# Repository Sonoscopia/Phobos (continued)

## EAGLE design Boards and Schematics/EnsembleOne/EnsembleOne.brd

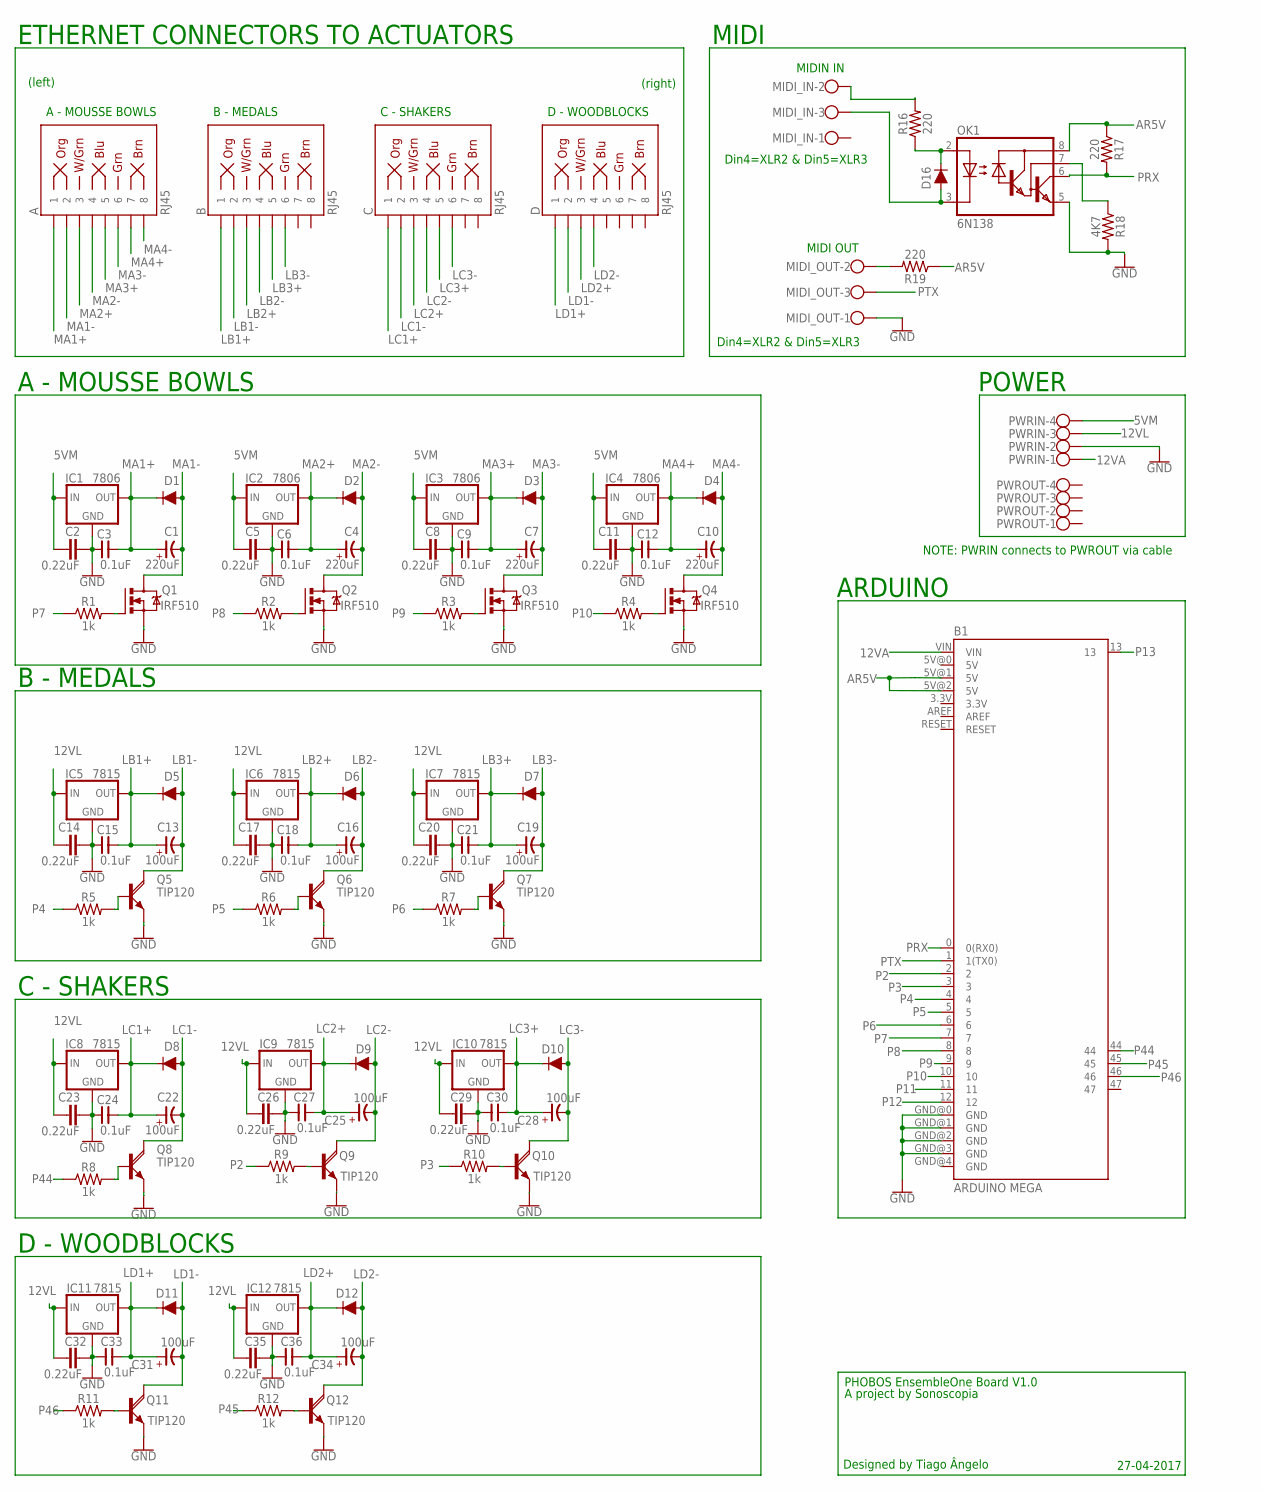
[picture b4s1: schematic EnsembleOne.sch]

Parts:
A: RJ45; RJ45-8
B: RJ45; RJ45-8
B1: ARDUINO MEGA; ENSEMBLE_ONE_ARDUINO_MEGA
C: RJ45; RJ45-8
C1, C4, C7, C10: 220uF; E-035X080
C2, C5, C8, C11, C14, C17, C20, C23, C26, C29, C32, C35: 0.22uF; C5B3
C3, C6, C9, C12, C15, C18, C21, C24, C27, C30, C33, C36: 0.1uF; C025-050X025
C13, C16, C19, C22: 100uF; CAP-MASTER_E-020X050
C25, C28, C31, C34: 100uF; E-020X050
D: RJ45; RJ45-8
D1, D2, D3, D4, D5, D6, D7, D8, D9, D10, D11, D12: 1A/50V/1.1V; DIODE-1N4001-KIT
D16: 200mA/100V/1V; DIODE-1N4148
IC1, IC2, IC3, IC4: 7806; 78XXS
IC5, IC6, IC7, IC8, IC9, IC10, IC11, IC12: 7815; 78XXS
MIDI_IN: W237-103
MIDI_OUT: W237-103
OK1: 6N138; DIL08
PWRIN: W237-4
PWROUT: W237-4
Q1, Q2, Q3, Q4: IRF510; TO220BV
Q5, Q6, Q7, Q8: TIP120; ROCKETFARM_TO220AV
Q9, Q10, Q11, Q12: TIP120; TO220AV
R1, R2, R3, R4, R5, R6, R7, R8, R9, R10, R11, R12: 1k; AXIAL-0.1
R16, R17, R19: 220; AXIAL-0.3
R18: 4K7; AXIAL-0.3

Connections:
5VM: C2.1, C5.1, C8.1, C11.1, IC1.IN, IC2.IN, IC3.IN, IC4.IN, PWRIN.4
12VA: B1.VIN, PWRIN.1
12VL: C14.1, C17.1, C20.1, C23.1, C26.1, C29.1, C32.1, C35.1, IC5.IN, IC6.IN, IC7.IN, IC8.IN, IC9.IN, IC10.IN, IC11.IN, IC12.IN, PWRIN.3
AR5V: B1.5V@1 (5V), B1.5V@2 (5V), OK1.8 (VCC), R17.P$1 (1), R19.P$1 (1)
GND: B1.GND@0 (GND), B1.GND@1 (GND), B1.GND@2 (GND), B1.GND@3 (GND), C2.2, C3.1, C5.2, C6.1, C8.2, C9.1, C11.2, C12.1, C14.2, C15.1, C17.2, C18.1, C20.2, C21.1, C23.2, C24.1, C26.2, C27.1, C29.2, C30.1, C32.2, C33.1, C35.2, C36.1, IC1.GND, IC2.GND, IC3.GND, IC4.GND, IC5.GND, IC6.GND, IC7.GND, IC8.GND, IC9.GND, IC10.GND, IC11.GND, IC12.GND, MIDI_OUT.1, OK1.5 (GND), PWRIN.2, Q1.S, Q2.S, Q3.S, Q4.S, Q5.E, Q6.E, Q7.E, Q8.E, Q9.E, Q10.E, Q11.E, Q12.E, R18.P$2 (2)
LB1+: B.1, C13.+, C15.2, D5.C, IC5.OUT
LB1-: B.2, C13.-, D5.A, Q5.C
LB2+: B.3, C16.+, C18.2, D6.C, IC6.OUT
LB2-: B.4, C16.-, D6.A, Q6.C
LB3+: B.5, C19.+, C21.2, D7.C, IC7.OUT
LB3-: B.6, C19.-, D7.A, Q7.C
LC1+: C.1, C22.+, C24.2, D8.C, IC8.OUT
LC1-: C.2, C22.-, D8.A, Q8.C
LC2+: C.3, C25.+, C27.2, D9.C, IC9.OUT
LC2-: C.4, C25.-, D9.A, Q9.C
LC3+: C.5, C28.+, C30.2, D10.C, IC10.OUT
LC3-: C.6, C28.-, D10.A, Q10.C
LD1+: C31.+, C33.2, D.1, D11.C, IC11.OUT
LD1-: C31.-, D.2, D11.A, Q11.C
LD2+: C34.+, C36.2, D.3, D12.C, IC12.OUT
LD2-: C34.-, D.4, D12.A, Q12.C
MA1+: A.1, C1.+, C3.2, D1.C, IC1.OUT
MA1-: A.2, C1.-, D1.A, Q1.D
MA2+: A.3, C4.+, C6.2, D2.C, IC2.OUT
MA2-: A.4, C4.-, D2.A, Q2.D
MA3+: A.5, C7.+, C9.2, D3.C, IC3.OUT
MA3-: A.6, C7.-, D3.A, Q3.D
MA4+: A.7, C10.+, C12.2, D4.C, IC4.OUT
MA4-: A.8, C10.-, D4.A, Q4.D
unnamed: Q1.G, R1.P$2 (2)
unnamed: MIDI_OUT.2, R19.P$2 (2)
unnamed: Q2.G, R2.P$2 (2)
unnamed: Q10.B, R10.P$2 (2)
unnamed: Q11.B, R11.P$2 (2)
unnamed: Q9.B, R9.P$2 (2)
unnamed: Q3.G, R3.P$2 (2)
unnamed: Q4.G, R4.P$2 (2)
unnamed: Q5.B, R5.P$2 (2)
unnamed: Q6.B, R6.P$2 (2)
unnamed: Q7.B, R7.P$2 (2)
unnamed: Q8.B, R8.P$2 (2)
unnamed: Q12.B, R12.P$2 (2)
unnamed: D16.A, MIDI_IN.3, OK1.3 (C)
unnamed: D16.C, OK1.2 (A), R16.P$1 (1)
unnamed: MIDI_IN.2, R16.P$2 (2)
unnamed: OK1.7 (VB), R18.P$1 (1)
P2: B1.2, R9.P$1 (1)
P3: B1.3, R10.P$1 (1)
P4: B1.4, R5.P$1 (1)
P5: B1.5, R6.P$1 (1)
P6: B1.6, R7.P$1 (1)
P7: B1.7, R1.P$1 (1)
P8: B1.8, R2.P$1 (1)
P9: B1.9, R3.P$1 (1)
P10: B1.10, R4.P$1 (1)
P11: B1.11
P12: B1.12
P13: B1.13
P44: B1.44, R8.P$1 (1)
P45: B1.45, R12.P$1 (1)
P46: B1.46, R11.P$1 (1)
PRX: B1.0 (0(RX0)), OK1.6 (VO), R17.P$2 (2)
PTX: B1.1 (1(TX0)), MIDI_OUT.3

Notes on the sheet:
Din4=XLR2 & Din5=XLR3
MIDI OUT
MIDIN IN
POWER
MIDI
ARDUINO
(right)
(left)
ETHERNET CONNECTORS TO ACTUATORS
D - WOODBLOCKS
C - SHAKERS
B - MEDALS
A - MOUSSE BOWLS
PHOBOS EnsembleOne Board V1.0
Designed by Tiago Ângelo
A project by Sonoscopia
27-04-2017
NOTE: PWRIN connects to PWROUT via cable

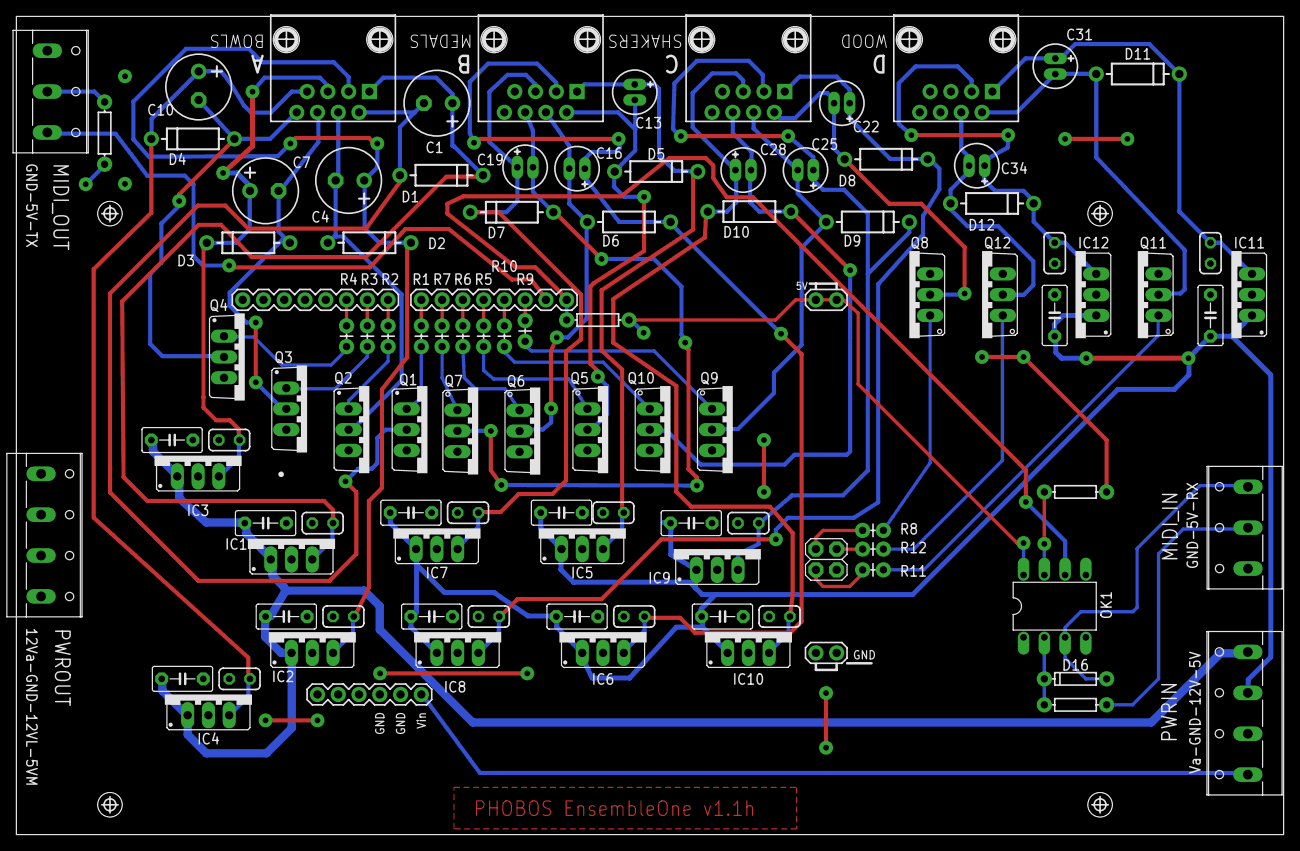
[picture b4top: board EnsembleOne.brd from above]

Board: 2 copper layers, 155.0 x 100.1 mm, 99 parts (0 on the bottom side), 60 nets.

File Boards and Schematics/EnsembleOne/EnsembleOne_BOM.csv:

Partlist exported from C:/Users/tiago/Documents/eagle/PHOBOS/EnsembleOne/EnsembleOne.sch at 05-05-2017 15:47

Qty Value         Device                  Package              Parts                                                   Description               MF                MPN     OC_FARNELL OC_NEWARK PROD_ID    SF_ID     VALUE        
2                 W237-103                W237-103             XIN, XOUT                                               WAGO SCREW CLAMP                            237-103 unknown    18M7116                                     
2                 W237-4                  W237-4               PWRIN, PWROUT                                           WAGO SCREW CLAMP                                    unknown    unknown                                     
12  0.1uF         CNP-C025-050X025        C025-050X025         C3, C6, C9, C12, C15, C18, C21, C24, C27, C30, C33, C36 NON-POLARIZED CAP                                                                                          
12  0.22uF        C5/3                    C5B3                 C2, C5, C8, C11, C14, C17, C20, C23, C26, C29, C32, C35 CAPACITOR                                                                                                  
4   100uF         CAP-MASTER_CP-E-020X050 CAP-MASTER_E-020X050 C13, C16, C19, C22                                      POLARIZED CAP                                                                                              
4   100uF         CP-E-020X050            E-020X050            C25, C28, C31, C34                                      POLARIZED CAP                                                                                              
12  1A/50V/1.1V   DIODE-KIT2              DIODE-1N4001-KIT     D1, D2, D3, D4, D5, D6, D7, D8, D9, D10, D11, D12       Diode                                                                    DIO-09176            1A/50V/1.1V  
12  1k            1KOHM-VERT-1/4W-1%      AXIAL-0.1            R1, R2, R3, R4, R5, R6, R7, R8, R9, R10, R11, R12       1kO resistor                                                             RES-12182            1k           
1   200mA/100V/1V DIODE-1N4148            DIODE-1N4148         D16                                                     Diode                                                                    DIO-08378            200mA/100V/1V
3   220           1KOHM-HORIZ-1/4W-5%     AXIAL-0.3            R16, R17, R19                                           1kO resistor                                                             RES-08380            1k           
4   220uF         CP-E-035X080            E-035X080            C1, C4, C7, C10                                         POLARIZED CAP                                                                                              
1   4K7           1KOHM-HORIZ-1/4W-5%     AXIAL-0.3            R18                                                     1kO resistor                                                             RES-08380            1k           
1   6N138         6N138                   DIL08                OK1                                                     MOTOROLA OPTO COUPLER     VISHAY/TELEFUNKEN 6N138   9860150    35K5294                                     
4   7806          78XXS                   78XXS                IC1, IC2, IC3, IC4                                      VOLTAGE REGULATOR                                                                                          
8   7815          78XXS                   78XXS                IC5, IC6, IC7, IC8, IC9, IC10, IC11, IC12               VOLTAGE REGULATOR                                                                                          
1   ARDUINO MEGA  ARDUINO_MEGA_R3FULL     ARDUINO_MEGA         B1                                                      Arduino Mega R3                                                                                            
4   IRF510        IRF520                  TO220BV              Q1, Q2, Q3, Q4                                          HEXFET Power MOSFET                                                                                        
4   RJ45          RJ45-8                  RJ45-8               A, B, C, D                                              RJ45 Jack - 8 pin                                                        CONN-08506 PRT-00643 RJ45         
4   TIP120        ROCKETFARM_TIP120V      ROCKETFARM_TO220AV   Q5, Q6, Q7, Q8                                          NPN DARLINGTON TRANSISTOR                                                                                  
4   TIP120        TIP120V                 TO220AV              Q9, Q10, Q11, Q12                                       NPN DARLINGTON TRANSISTOR

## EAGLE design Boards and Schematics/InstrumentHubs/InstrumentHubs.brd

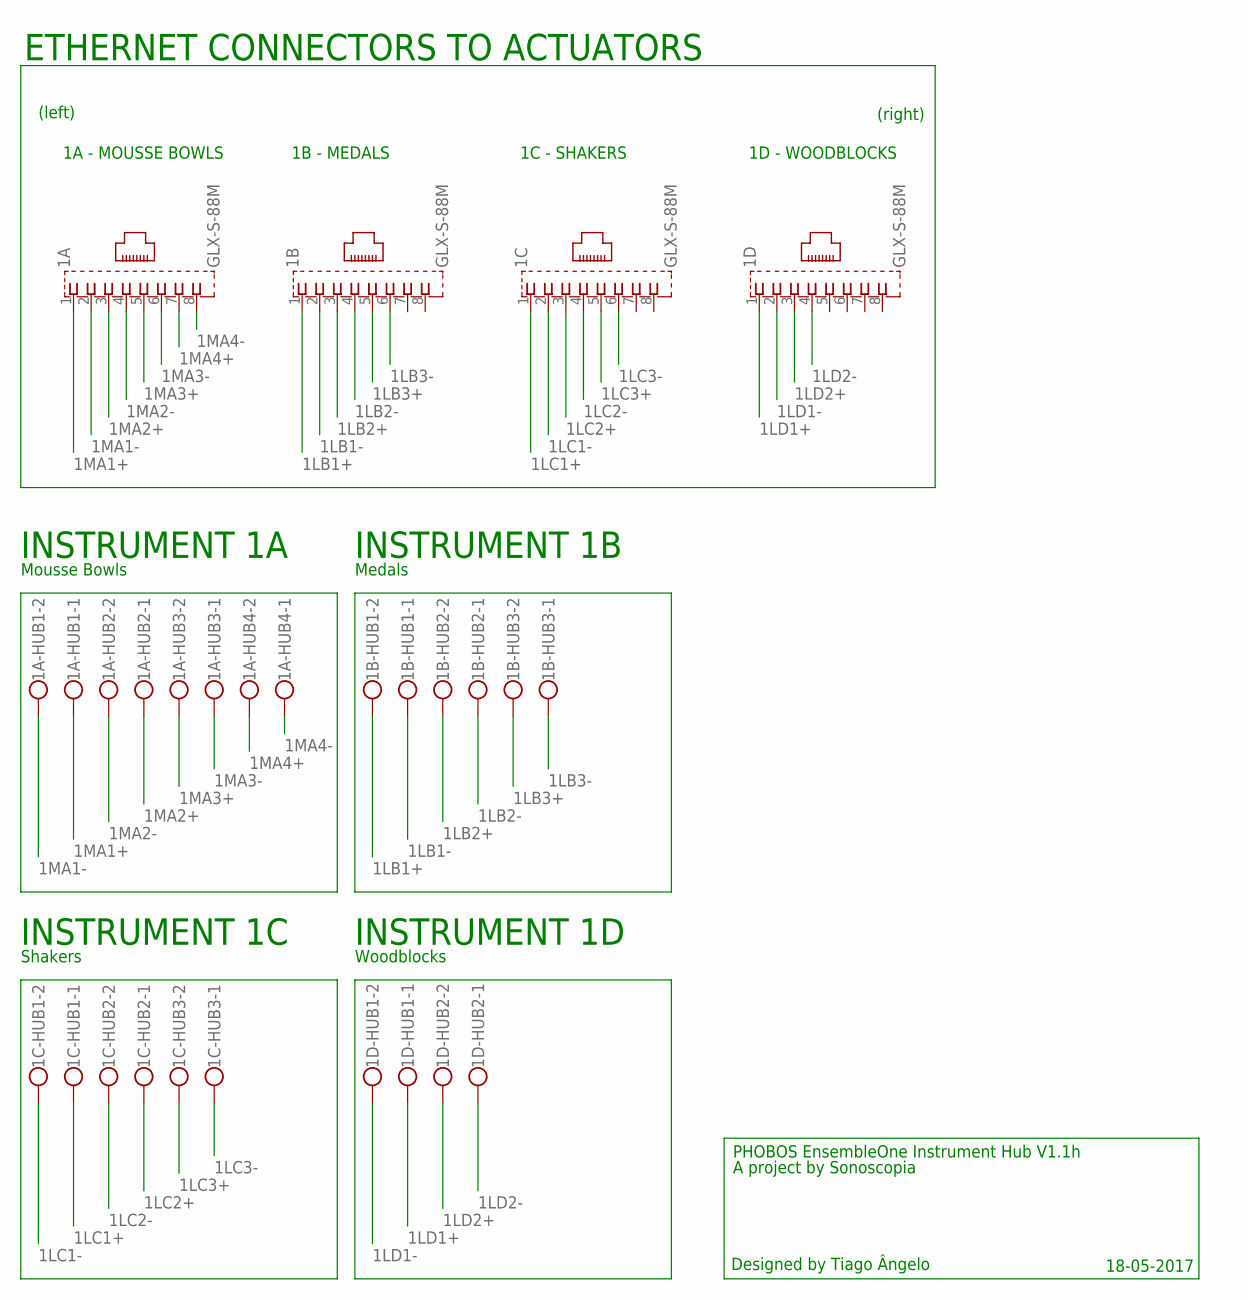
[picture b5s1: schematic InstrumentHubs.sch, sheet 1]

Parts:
1A, 1B, 1C, 1D: GLX-S-88M
1A-HUB1, 1A-HUB2, 1A-HUB3, 1A-HUB4, 1B-HUB1, 1B-HUB2, 1B-HUB3, 1C-HUB1, 1C-HUB2, 1C-HUB3, 1D-HUB1, 1D-HUB2: W237-102

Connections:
1LB1+: 1B.1, 1B-HUB1.2
1LB1-: 1B.2, 1B-HUB1.1
1LB2+: 1B.3, 1B-HUB2.2
1LB2-: 1B.4, 1B-HUB2.1
1LB3+: 1B.5, 1B-HUB3.2
1LB3-: 1B.6, 1B-HUB3.1
1LC1+: 1C.1, 1C-HUB1.1
1LC1-: 1C.2, 1C-HUB1.2
1LC2+: 1C.3, 1C-HUB2.1
1LC2-: 1C.4, 1C-HUB2.2
1LC3+: 1C.5, 1C-HUB3.2
1LC3-: 1C.6, 1C-HUB3.1
1LD1+: 1D.1, 1D-HUB1.1
1LD1-: 1D.2, 1D-HUB1.2
1LD2+: 1D.3, 1D-HUB2.2
1LD2-: 1D.4, 1D-HUB2.1
1MA1+: 1A.1, 1A-HUB1.1
1MA1-: 1A.2, 1A-HUB1.2
1MA2+: 1A.3, 1A-HUB2.1
1MA2-: 1A.4, 1A-HUB2.2
1MA3+: 1A.5, 1A-HUB3.2
1MA3-: 1A.6, 1A-HUB3.1
1MA4+: 1A.7, 1A-HUB4.2
1MA4-: 1A.8, 1A-HUB4.1

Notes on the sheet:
INSTRUMENT 1A
(right)
(left)
ETHERNET CONNECTORS TO ACTUATORS
1D - WOODBLOCKS
1C - SHAKERS
1B - MEDALS
1A - MOUSSE BOWLS
PHOBOS EnsembleOne Instrument Hub V1.1h
Designed by Tiago Ângelo
A project by Sonoscopia
Mousse Bowls
INSTRUMENT 1B
Medals
INSTRUMENT 1C
Shakers
INSTRUMENT 1D
Woodblocks
18-05-2017

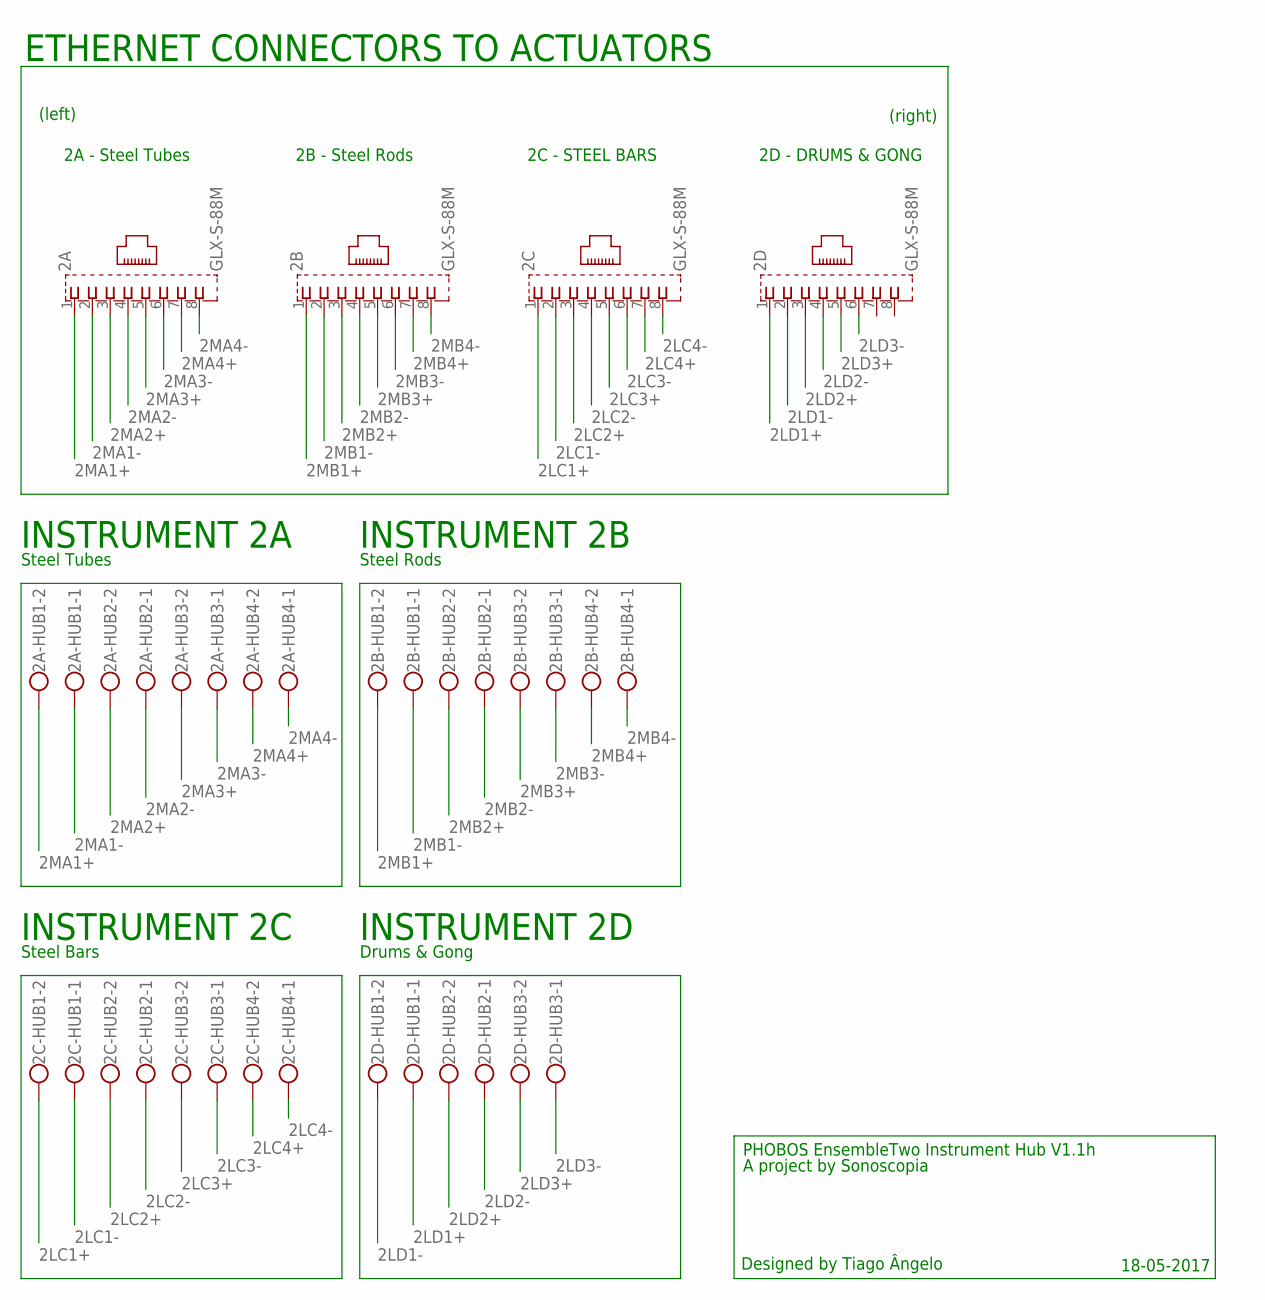
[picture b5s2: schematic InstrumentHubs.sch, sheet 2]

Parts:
2A, 2B, 2C, 2D: GLX-S-88M
2A-HUB1, 2A-HUB2, 2A-HUB3, 2A-HUB4, 2B-HUB1, 2B-HUB2, 2B-HUB3, 2B-HUB4, 2C-HUB1, 2C-HUB2, 2C-HUB3, 2C-HUB4, 2D-HUB1, 2D-HUB2, 2D-HUB3: W237-102

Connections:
2LC1+: 2C.1, 2C-HUB1.2
2LC1-: 2C.2, 2C-HUB1.1
2LC2+: 2C.3, 2C-HUB2.2
2LC2-: 2C.4, 2C-HUB2.1
2LC3+: 2C.5, 2C-HUB3.2
2LC3-: 2C.6, 2C-HUB3.1
2LC4+: 2C.7, 2C-HUB4.2
2LC4-: 2C.8, 2C-HUB4.1
2LD1+: 2D.1, 2D-HUB1.1
2LD1-: 2D.2, 2D-HUB1.2
2LD2+: 2D.3, 2D-HUB2.2
2LD2-: 2D.4, 2D-HUB2.1
2LD3+: 2D.5, 2D-HUB3.2
2LD3-: 2D.6, 2D-HUB3.1
2MA1+: 2A.1, 2A-HUB1.2
2MA1-: 2A.2, 2A-HUB1.1
2MA2+: 2A.3, 2A-HUB2.2
2MA2-: 2A.4, 2A-HUB2.1
2MA3+: 2A.5, 2A-HUB3.2
2MA3-: 2A.6, 2A-HUB3.1
2MA4+: 2A.7, 2A-HUB4.2
2MA4-: 2A.8, 2A-HUB4.1
2MB1+: 2B.1, 2B-HUB1.2
2MB1-: 2B.2, 2B-HUB1.1
2MB2+: 2B.3, 2B-HUB2.2
2MB2-: 2B.4, 2B-HUB2.1
2MB3+: 2B.5, 2B-HUB3.2
2MB3-: 2B.6, 2B-HUB3.1
2MB4+: 2B.7, 2B-HUB4.2
2MB4-: 2B.8, 2B-HUB4.1

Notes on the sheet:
INSTRUMENT 2A
PHOBOS EnsembleTwo Instrument Hub V1.1h
Designed by Tiago Ângelo
A project by Sonoscopia
18-05-2017
Steel Tubes
INSTRUMENT 2B
Steel Rods
INSTRUMENT 2C
Steel Bars
INSTRUMENT 2D
Drums & Gong
(right)
(left)
ETHERNET CONNECTORS TO ACTUATORS
2D - DRUMS & GONG
2C - STEEL BARS
2B - Steel Rods
2A - Steel Tubes

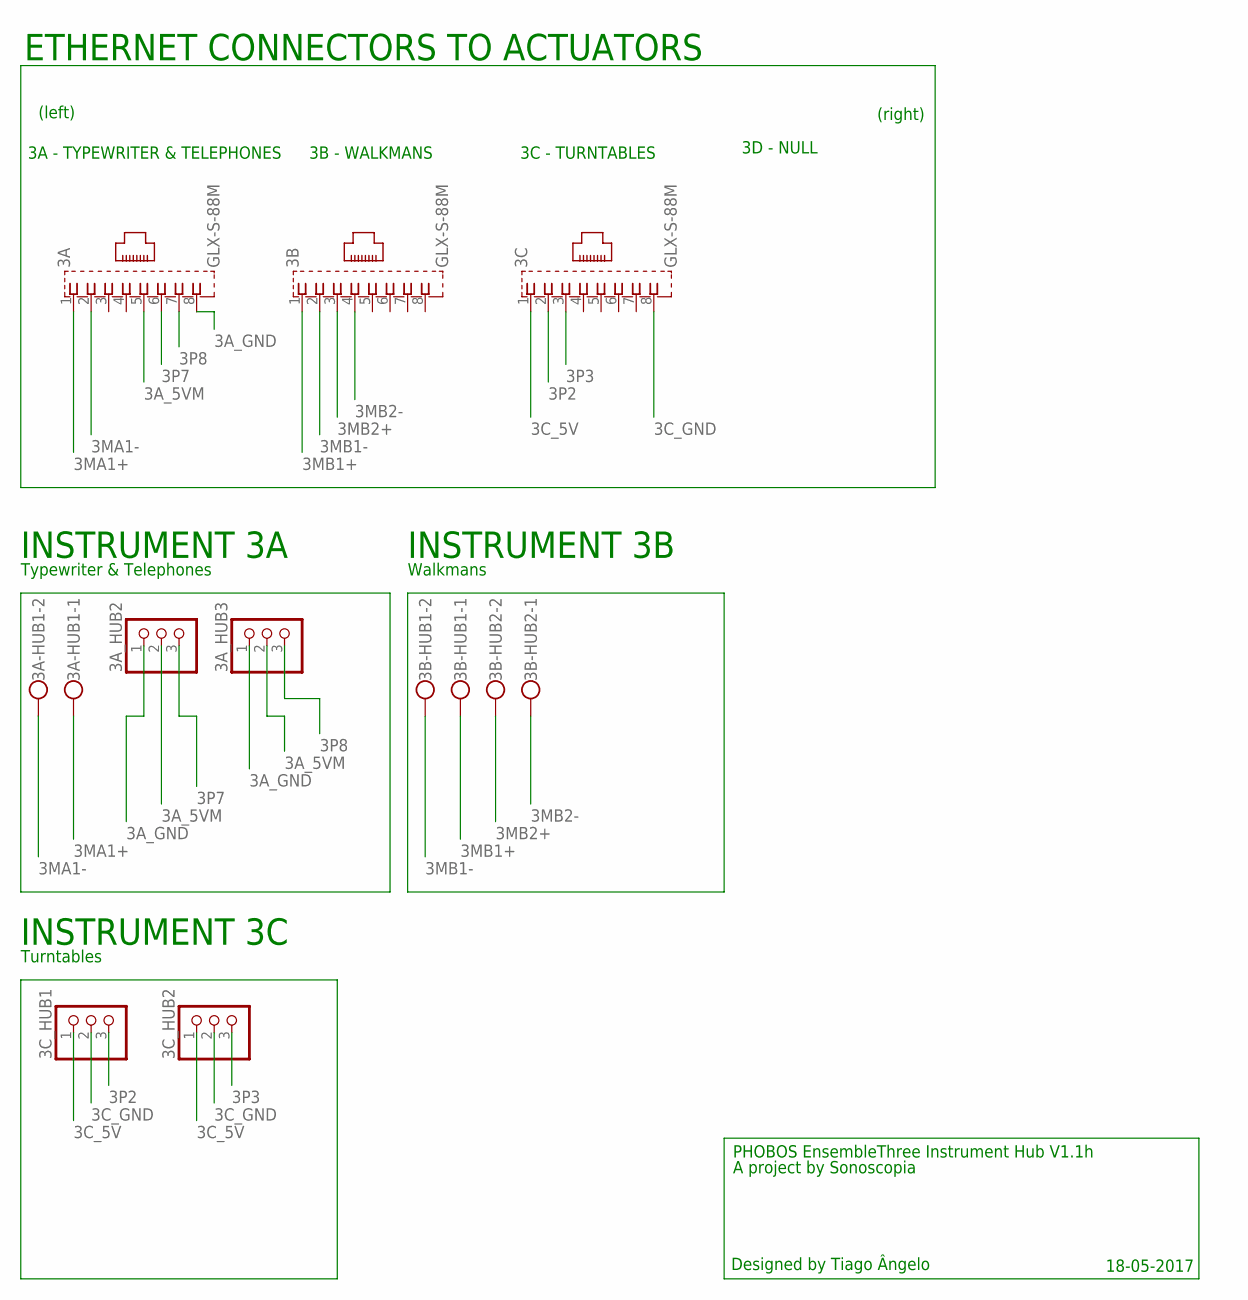
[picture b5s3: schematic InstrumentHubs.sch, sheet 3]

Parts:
3A, 3B, 3C: GLX-S-88M
3A-HUB1, 3B-HUB1, 3B-HUB2: W237-102
3A_HUB2, 3A_HUB3, 3C_HUB1, 3C_HUB2: PINHD-1X3; 1X03

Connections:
3A_5VM: 3A.5, 3A_HUB2.2, 3A_HUB3.2
3A_GND: 3A.8, 3A_HUB2.1, 3A_HUB3.1
3C_5V: 3C.1, 3C_HUB1.1, 3C_HUB2.1
3C_GND: 3C.8, 3C_HUB1.2, 3C_HUB2.2
3MA1+: 3A.1, 3A-HUB1.1
3MA1-: 3A.2, 3A-HUB1.2
3MB1+: 3B.1, 3B-HUB1.1
3MB1-: 3B.2, 3B-HUB1.2
3MB2+: 3B.3, 3B-HUB2.2
3MB2-: 3B.4, 3B-HUB2.1
3P2: 3C.2, 3C_HUB1.3
3P3: 3C.3, 3C_HUB2.3
3P7: 3A.6, 3A_HUB2.3
3P8: 3A.7, 3A_HUB3.3

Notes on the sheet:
INSTRUMENT 3A
PHOBOS EnsembleThree Instrument Hub V1.1h
Designed by Tiago Ângelo
A project by Sonoscopia
18-05-2017
Typewriter & Telephones
INSTRUMENT 3B
Walkmans
INSTRUMENT 3C
Turntables
(right)
(left)
ETHERNET CONNECTORS TO ACTUATORS
3C - TURNTABLES
3B - WALKMANS
3A - TYPEWRITER & TELEPHONES
3D - NULL

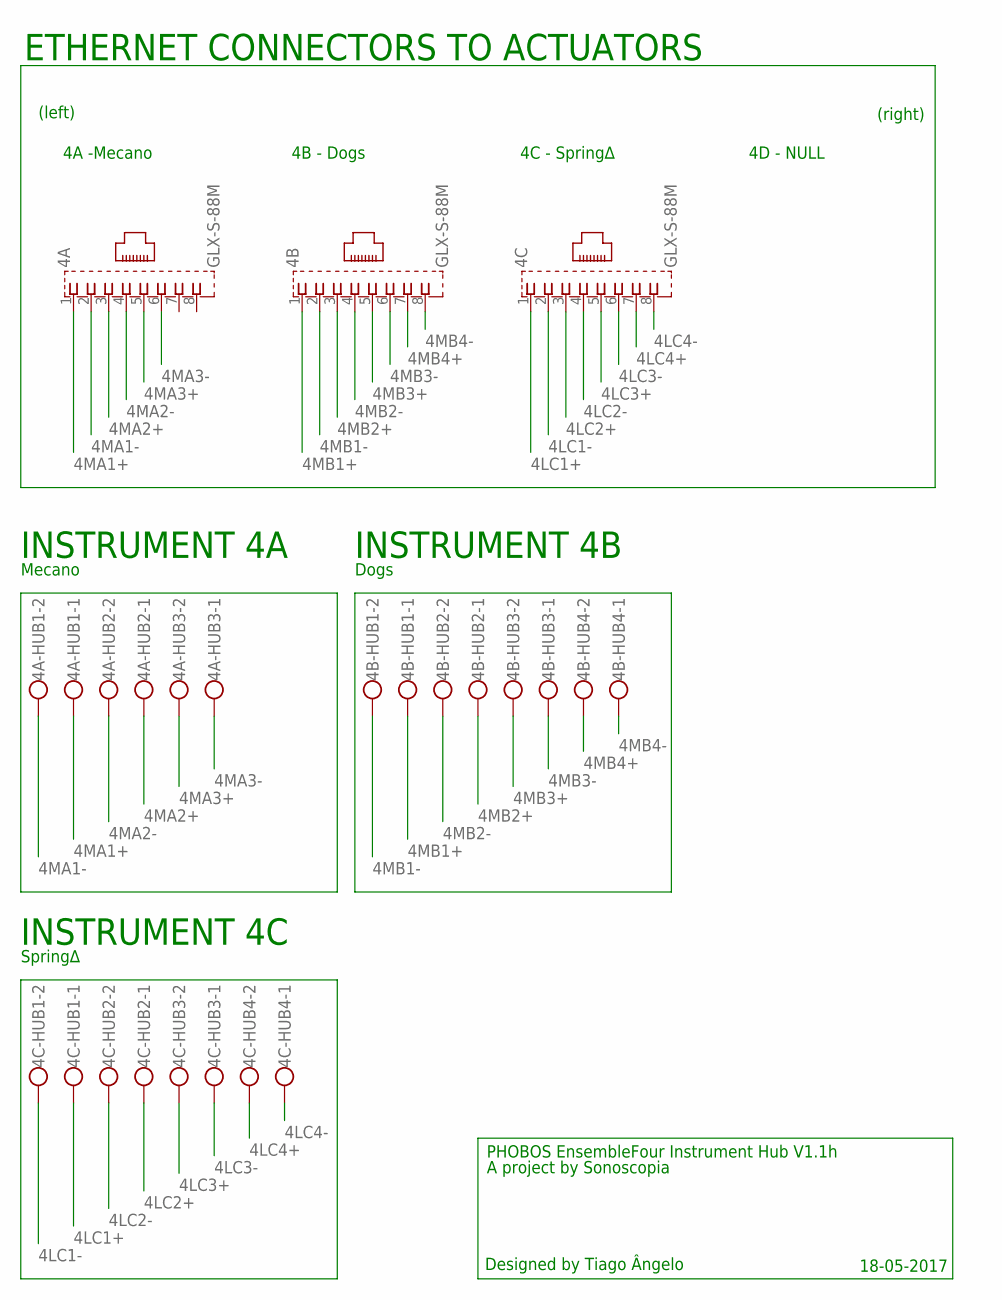
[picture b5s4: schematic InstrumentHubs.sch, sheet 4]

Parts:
4A, 4B, 4C: GLX-S-88M
4A-HUB1, 4A-HUB2, 4A-HUB3, 4B-HUB1, 4B-HUB2, 4B-HUB3, 4B-HUB4, 4C-HUB1, 4C-HUB2, 4C-HUB3, 4C-HUB4: W237-102

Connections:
4LC1+: 4C.1, 4C-HUB1.1
4LC1-: 4C.2, 4C-HUB1.2
4LC2+: 4C.3, 4C-HUB2.1
4LC2-: 4C.4, 4C-HUB2.2
4LC3+: 4C.5, 4C-HUB3.2
4LC3-: 4C.6, 4C-HUB3.1
4LC4+: 4C.7, 4C-HUB4.2
4LC4-: 4C.8, 4C-HUB4.1
4MA1+: 4A.1, 4A-HUB1.1
4MA1-: 4A.2, 4A-HUB1.2
4MA2+: 4A.3, 4A-HUB2.1
4MA2-: 4A.4, 4A-HUB2.2
4MA3+: 4A.5, 4A-HUB3.2
4MA3-: 4A.6, 4A-HUB3.1
4MB1+: 4B.1, 4B-HUB1.1
4MB1-: 4B.2, 4B-HUB1.2
4MB2+: 4B.3, 4B-HUB2.1
4MB2-: 4B.4, 4B-HUB2.2
4MB3+: 4B.5, 4B-HUB3.2
4MB3-: 4B.6, 4B-HUB3.1
4MB4+: 4B.7, 4B-HUB4.2
4MB4-: 4B.8, 4B-HUB4.1

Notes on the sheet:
INSTRUMENT 4A
PHOBOS EnsembleFour Instrument Hub V1.1h
Designed by Tiago Ângelo
A project by Sonoscopia
18-05-2017
Mecano
INSTRUMENT 4B
Dogs
INSTRUMENT 4C
Spring∆
(right)
(left)
ETHERNET CONNECTORS TO ACTUATORS
4D - NULL
4C - Spring∆
4B - Dogs
4A -Mecano

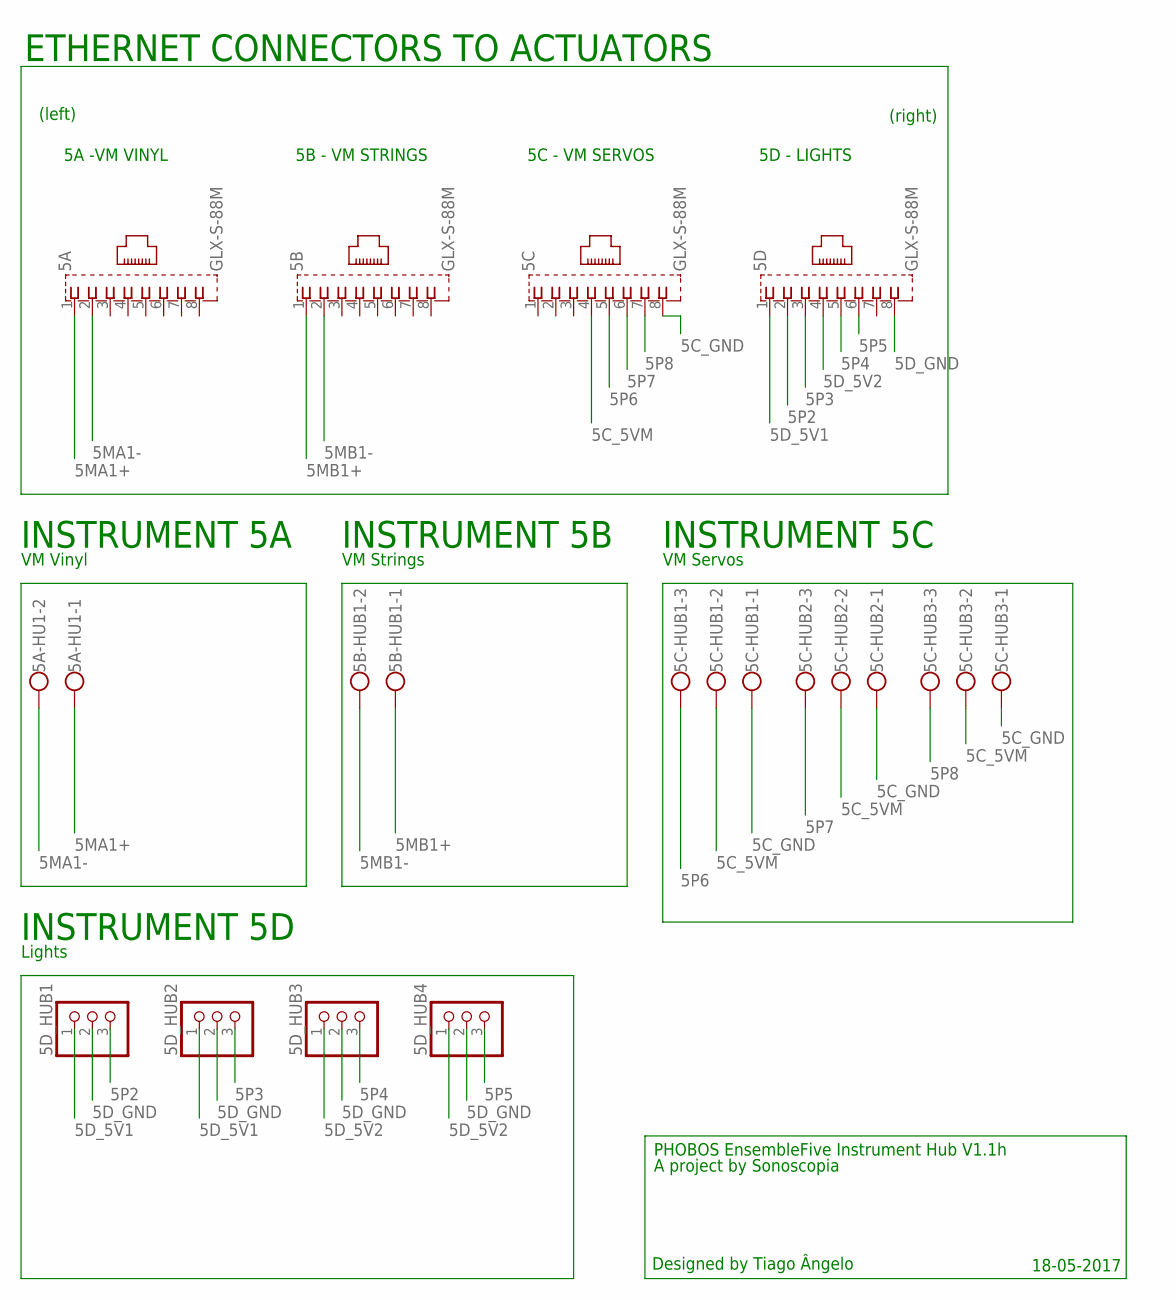
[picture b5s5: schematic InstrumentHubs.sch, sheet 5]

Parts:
5A, 5B, 5C, 5D: GLX-S-88M
5A-HU1, 5B-HUB1: W237-102
5C-HUB1, 5C-HUB2, 5C-HUB3: W237-103
5D_HUB1, 5D_HUB2, 5D_HUB3, 5D_HUB4: PINHD-1X3; 1X03

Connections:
5C_5VM: 5C.4, 5C-HUB1.2, 5C-HUB2.2, 5C-HUB3.2
5C_GND: 5C.8, 5C-HUB1.1, 5C-HUB2.1, 5C-HUB3.1
5D_5V1: 5D.1, 5D_HUB1.1, 5D_HUB2.1
5D_5V2: 5D.4, 5D_HUB3.1, 5D_HUB4.1
5D_GND: 5D.8, 5D_HUB1.2, 5D_HUB2.2, 5D_HUB3.2, 5D_HUB4.2
5MA1+: 5A.1, 5A-HU1.1
5MA1-: 5A.2, 5A-HU1.2
5MB1+: 5B.1, 5B-HUB1.1
5MB1-: 5B.2, 5B-HUB1.2
5P2: 5D.2, 5D_HUB1.3
5P3: 5D.3, 5D_HUB2.3
5P4: 5D.5, 5D_HUB3.3
5P5: 5D.6, 5D_HUB4.3
5P6: 5C.5, 5C-HUB1.3
5P7: 5C.6, 5C-HUB2.3
5P8: 5C.7, 5C-HUB3.3

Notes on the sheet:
INSTRUMENT 5A
PHOBOS EnsembleFive Instrument Hub V1.1h
Designed by Tiago Ângelo
A project by Sonoscopia
18-05-2017
VM Vinyl
INSTRUMENT 5B
VM Strings
INSTRUMENT 5C
VM Servos
(right)
(left)
ETHERNET CONNECTORS TO ACTUATORS
5D - LIGHTS
5C - VM SERVOS
5B - VM STRINGS
5A -VM VINYL
INSTRUMENT 5D
Lights

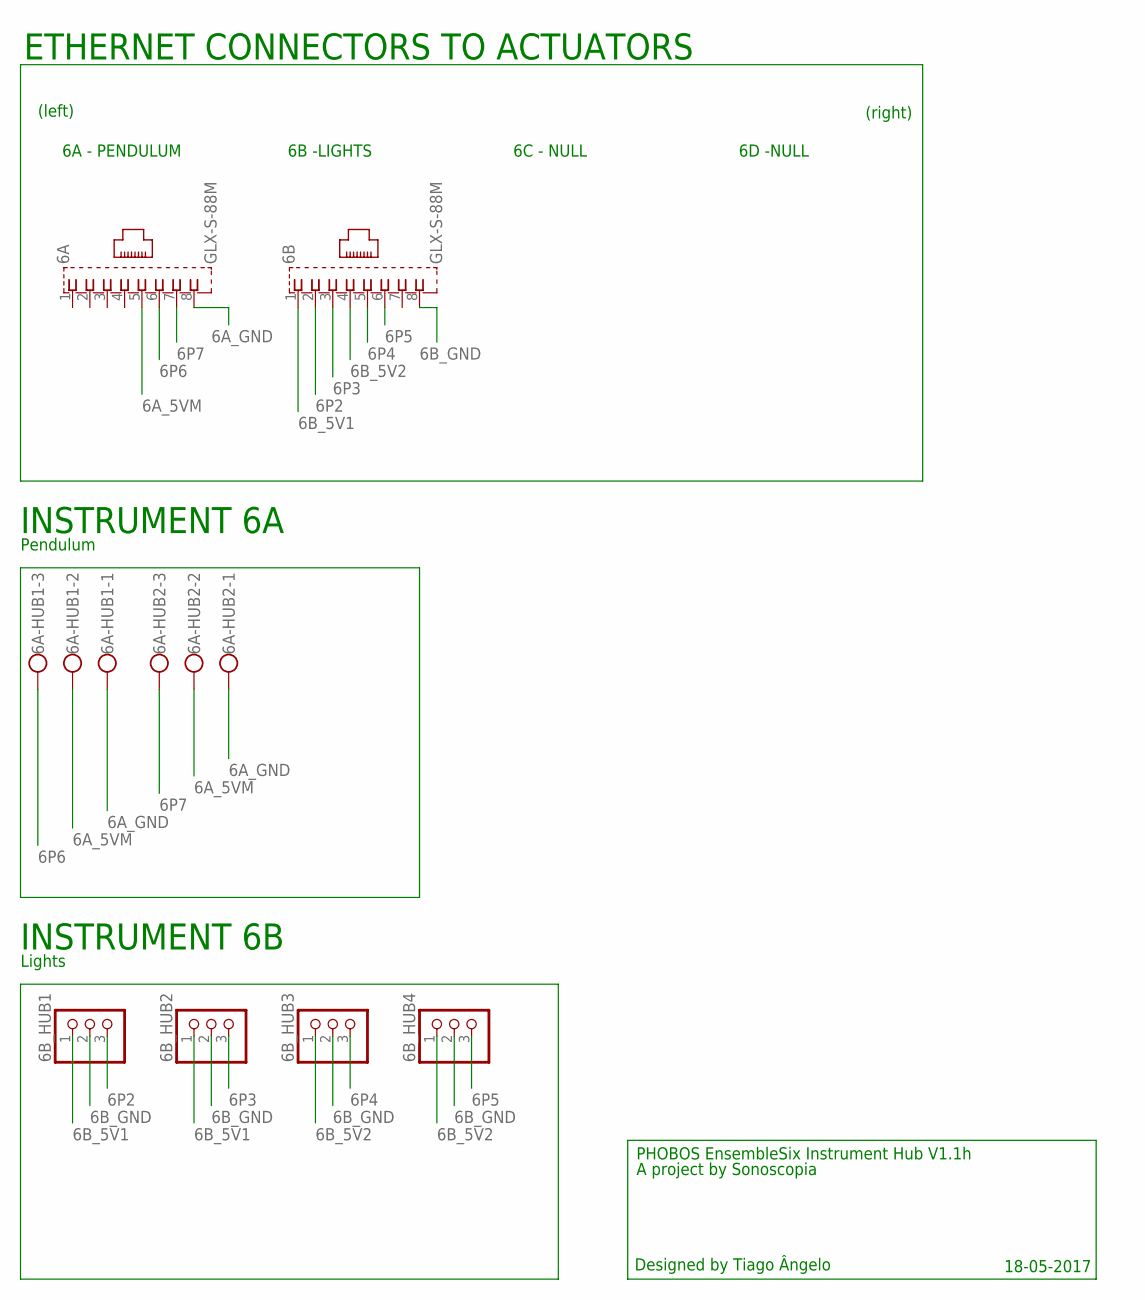
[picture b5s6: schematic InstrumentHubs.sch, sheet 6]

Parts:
6A, 6B: GLX-S-88M
6A-HUB1, 6A-HUB2: W237-103
6B_HUB1, 6B_HUB2, 6B_HUB3, 6B_HUB4: PINHD-1X3; 1X03

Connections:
6A_5VM: 6A.5, 6A-HUB1.2, 6A-HUB2.2
6A_GND: 6A.8, 6A-HUB1.1, 6A-HUB2.1
6B_5V1: 6B.1, 6B_HUB1.1, 6B_HUB2.1
6B_5V2: 6B.4, 6B_HUB3.1, 6B_HUB4.1
6B_GND: 6B.8, 6B_HUB1.2, 6B_HUB2.2, 6B_HUB3.2, 6B_HUB4.2
6P2: 6B.2, 6B_HUB1.3
6P3: 6B.3, 6B_HUB2.3
6P4: 6B.5, 6B_HUB3.3
6P5: 6B.6, 6B_HUB4.3
6P6: 6A.6, 6A-HUB1.3
6P7: 6A.7, 6A-HUB2.3

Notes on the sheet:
PHOBOS EnsembleSix Instrument Hub V1.1h
Designed by Tiago Ângelo
A project by Sonoscopia
18-05-2017
INSTRUMENT 6A
Pendulum
INSTRUMENT 6B
Lights
(right)
(left)
ETHERNET CONNECTORS TO ACTUATORS
6D -NULL
6C - NULL
6B -LIGHTS
6A - PENDULUM

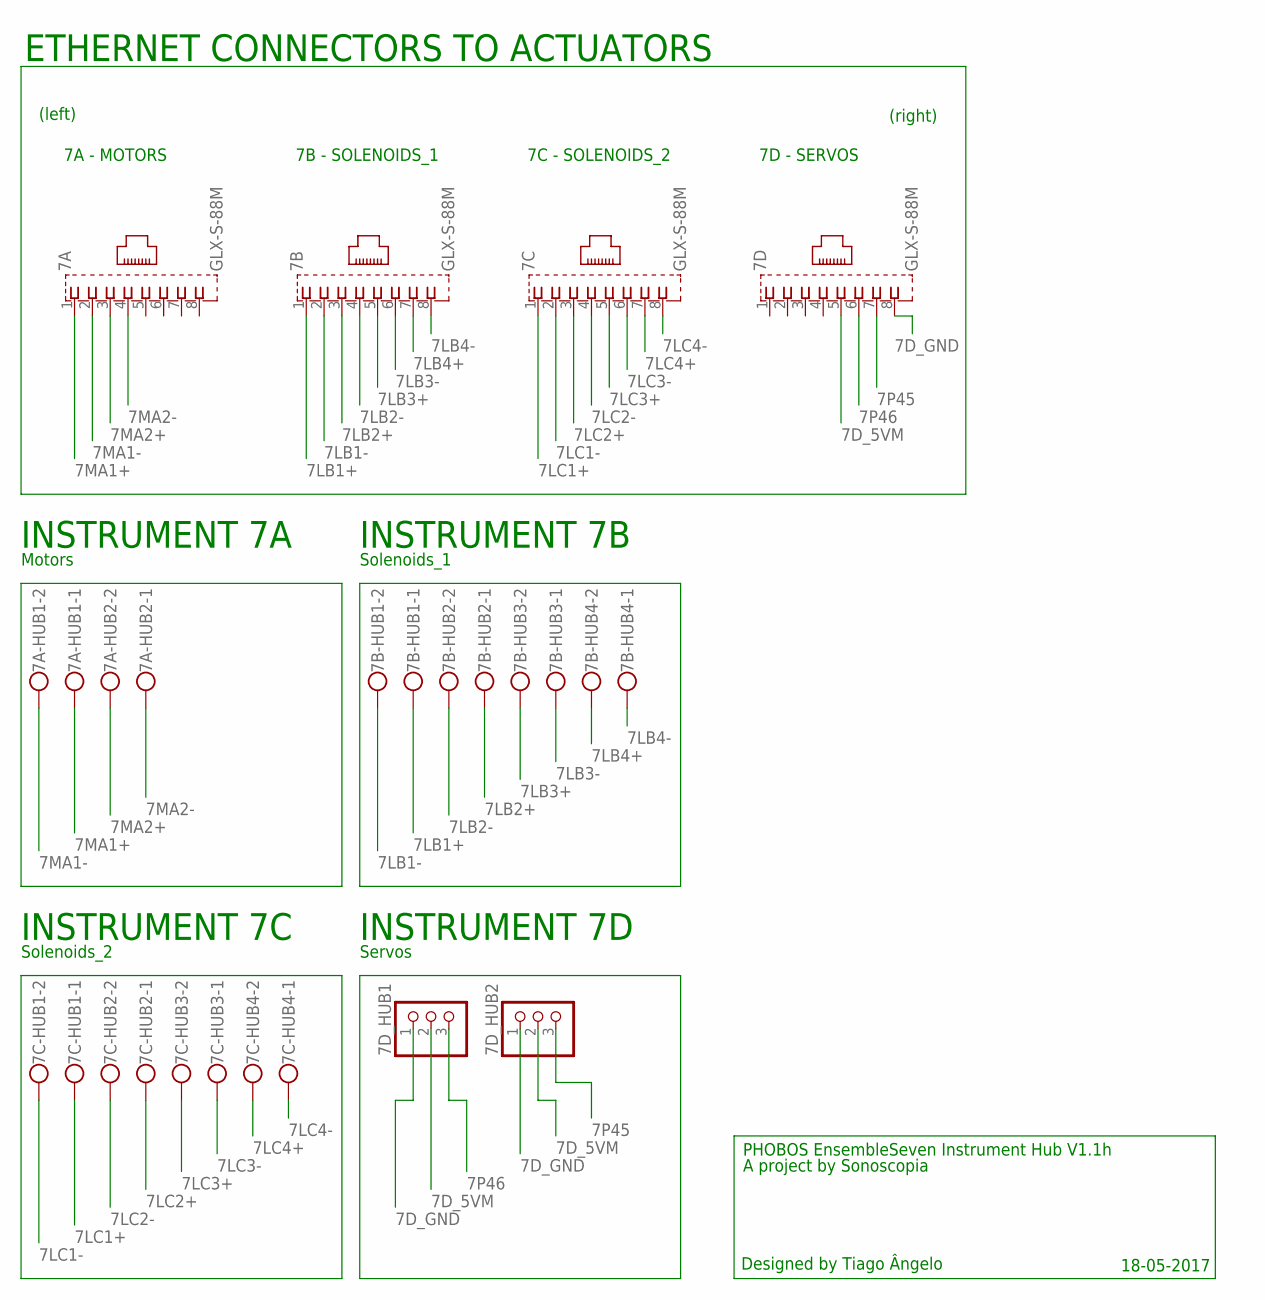
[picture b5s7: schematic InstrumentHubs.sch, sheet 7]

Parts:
7A, 7B, 7C, 7D: GLX-S-88M
7A-HUB1, 7A-HUB2, 7B-HUB1, 7B-HUB2, 7B-HUB3, 7B-HUB4, 7C-HUB1, 7C-HUB2, 7C-HUB3, 7C-HUB4: W237-102
7D_HUB1, 7D_HUB2: PINHD-1X3; 1X03

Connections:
7D_5VM: 7D.5, 7D_HUB1.2, 7D_HUB2.2
7D_GND: 7D.8, 7D_HUB1.1, 7D_HUB2.1
7LB1+: 7B.1, 7B-HUB1.1
7LB1-: 7B.2, 7B-HUB1.2
7LB2+: 7B.3, 7B-HUB2.1
7LB2-: 7B.4, 7B-HUB2.2
7LB3+: 7B.5, 7B-HUB3.2
7LB3-: 7B.6, 7B-HUB3.1
7LB4+: 7B.7, 7B-HUB4.2
7LB4-: 7B.8, 7B-HUB4.1
7LC1+: 7C.1, 7C-HUB1.1
7LC1-: 7C.2, 7C-HUB1.2
7LC2+: 7C.3, 7C-HUB2.1
7LC2-: 7C.4, 7C-HUB2.2
7LC3+: 7C.5, 7C-HUB3.2
7LC3-: 7C.6, 7C-HUB3.1
7LC4+: 7C.7, 7C-HUB4.2
7LC4-: 7C.8, 7C-HUB4.1
7MA1+: 7A.1, 7A-HUB1.1
7MA1-: 7A.2, 7A-HUB1.2
7MA2+: 7A.3, 7A-HUB2.2
7MA2-: 7A.4, 7A-HUB2.1
7P45: 7D.7, 7D_HUB2.3
7P46: 7D.6, 7D_HUB1.3

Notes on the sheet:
INSTRUMENT 7A
PHOBOS EnsembleSeven Instrument Hub V1.1h
Designed by Tiago Ângelo
A project by Sonoscopia
18-05-2017
Motors
INSTRUMENT 7B
Solenoids_1
INSTRUMENT 7C
Solenoids_2
INSTRUMENT 7D
Servos
(right)
(left)
ETHERNET CONNECTORS TO ACTUATORS
7D - SERVOS
7C - SOLENOIDS_2
7B - SOLENOIDS_1
7A - MOTORS
